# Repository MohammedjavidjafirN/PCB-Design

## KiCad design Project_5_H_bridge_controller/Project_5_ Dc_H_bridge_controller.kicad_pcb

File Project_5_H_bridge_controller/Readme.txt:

This project implements a 12V DC motor driver using an H-Bridge topology, designed to provide bidirectional control and speed regulation of a DC motor. The circuit integrates power electronics and embedded control, using an ESP32 microcontroller to generate PWM control signals and a TC4427A gate driver IC to efficiently drive the MOSFETs.
The H-Bridge is constructed using four N-channel MOSFETs (IRLZ24NPBF) arranged in a full-bridge configuration. This arrangement allows the polarity of the voltage across the motor to be reversed, enabling both forward and reverse rotation. The motor is powered using an external 12V supply, while the switching behavior is controlled through PWM signals from the ESP32.
The PWM signals are fed into the TC4427A dual MOSFET gate driver, which amplifies the control signals and provides sufficient current to rapidly charge and discharge the MOSFET gates. This ensures fast switching, reduced switching losses, and improved efficiency compared to directly driving MOSFETs from the microcontroller.

By controlling the switching sequence of the MOSFETs:

1.One diagonal pair of MOSFETs turns ON → motor rotates in one direction
2.The opposite diagonal pair turns ON → motor reverses direction
3.PWM applied to the enable path → controls motor speed

The design demonstrates a complete motor control system, combining high-current switching, logic-level control, and efficient gate driving

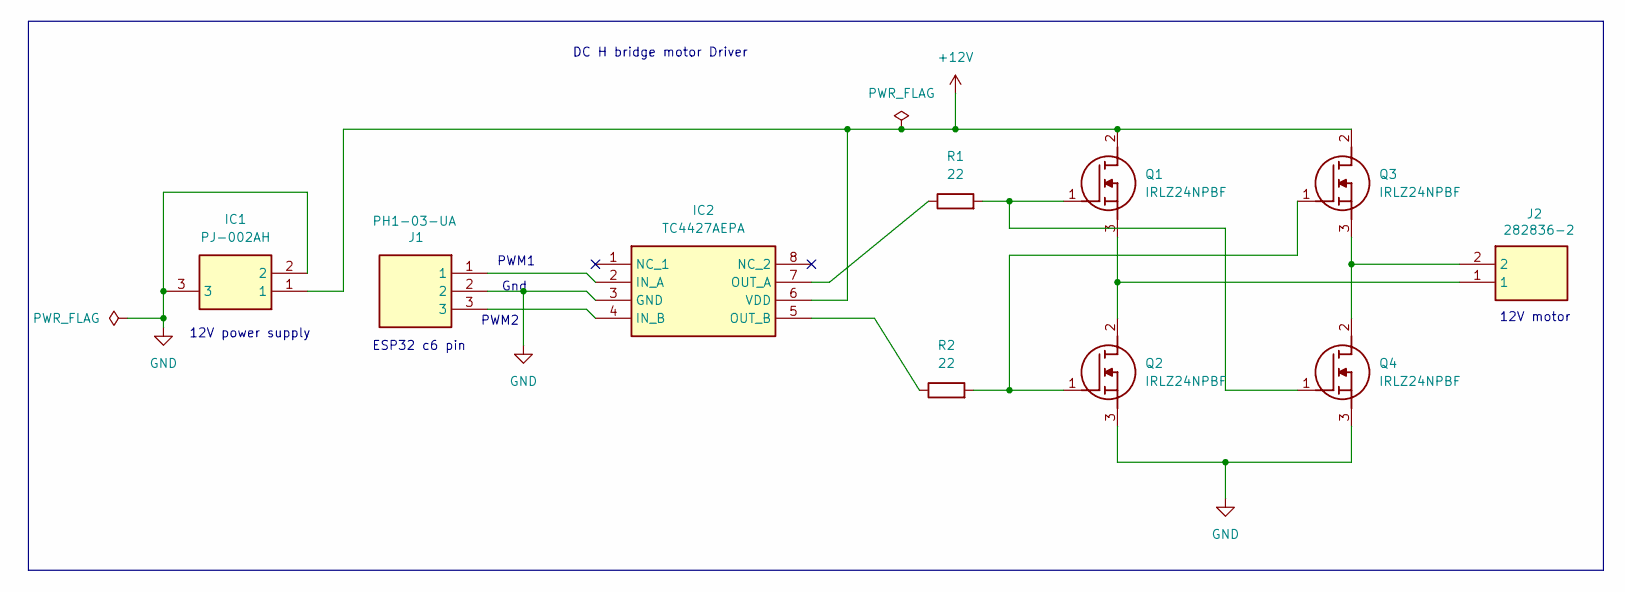
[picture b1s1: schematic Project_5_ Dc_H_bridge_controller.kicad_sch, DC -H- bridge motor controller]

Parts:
IC1: PJ-002AH; PJ002AH; Manufacturer_Part_Number PJ-002AH; Mouser Part Number 490-PJ-002AH
IC2: TC4427AEPA; Manufacturer_Part_Number TC4427AEPA; Mouser Part Number 579-TC4427AEPA
J1: PH1-03-UA; Manufacturer_Part_Number PH1-03-UA; Mouser Part Number 737-PH1-03-UA
J2: 282836-2; 2828362 V2; Manufacturer_Part_Number 282836-2; Mouser Part Number 571-2828362
Q1, Q2, Q3, Q4: IRLZ24NPBF; IRLZ24NBF; Manufacturer_Part_Number IRLZ24NPBF; Mouser Part Number 942-IRLZ24NPBF
R1, R2: 22; R_Axial_DIN0204_L3.6mm_D1.6mm_P5.08mm_Horizontal

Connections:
+12V: IC1.1, IC2.6 (VDD), Q1.2 (D), Q3.2 (D)
GND: IC1.2, IC1.3, IC2.3 (GND), J1.2, Q2.3 (S), Q4.3 (S)
unnamed: IC2.2 (IN_A), J1.1
unnamed: IC2.4 (IN_B), J1.3
unnamed: IC2.7 (OUT_A), R1.1
unnamed: IC2.5 (OUT_B), R2.1
unnamed: Q1.1 (G), Q4.1 (G), R1.2
unnamed: J2.1, Q1.3 (S), Q2.2 (D)
unnamed: Q2.1 (G), Q3.1 (G), R2.2
unnamed: J2.2, Q3.3 (S), Q4.2 (D)

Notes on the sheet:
PWM1
12V power supply
12V motor
PWM2
Gnd
DC H bridge motor Driver
ESP32 c6 pin

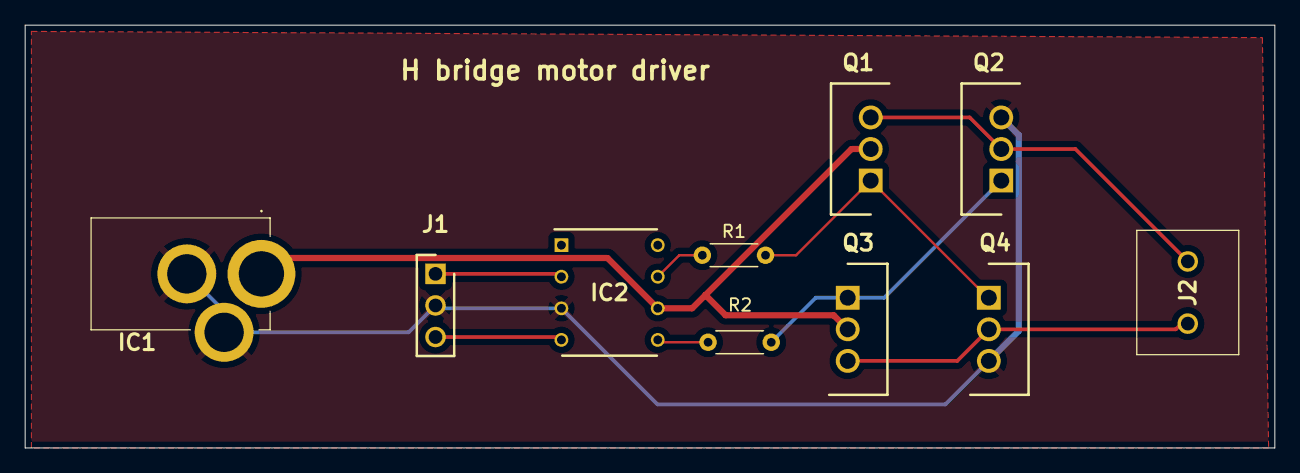
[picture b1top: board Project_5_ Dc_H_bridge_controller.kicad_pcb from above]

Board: 2 copper layers, 100.5 x 34.0 mm, 10 parts (0 on the bottom side), 10 nets.

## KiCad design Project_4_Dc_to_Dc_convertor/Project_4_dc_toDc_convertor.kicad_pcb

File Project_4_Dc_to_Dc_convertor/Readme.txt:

Project description:
This project implements a DC-DC Boost Converter designed to step up a 5V input supply to a regulated 12V output, primarily intended to drive loads such as a DC fan. The design integrates power electronics and embedded control, where the switching operation is driven by PWM signals from an ESP32 microcontroller.
The core of the circuit is based on a boost converter topology, consisting of an inductor, switching MOSFET, diode, and output capacitor. A gate driver IC (TC4427A) is used to efficiently drive the MOSFET, ensuring fast switching and reducing transition losses. The PWM signal from the ESP32 is fed into the gate driver, which amplifies the signal to provide sufficient current for driving the MOSFET gate.
During operation, when the MOSFET is switched ON, energy is stored in the inductor. When the MOSFET is switched OFF, the stored energy is released through the diode to the output capacitor, resulting in a boosted output voltage higher than the input. The output capacitor smooths the voltage, providing a stable DC output suitable for powering a 12V fan.
The switching frequency and duty cycle of the PWM signal control the output voltage, allowing dynamic adjustment of the boost level. This makes the system flexible for different load conditions and demonstrates real-time control of power conversion using a microcontroller.

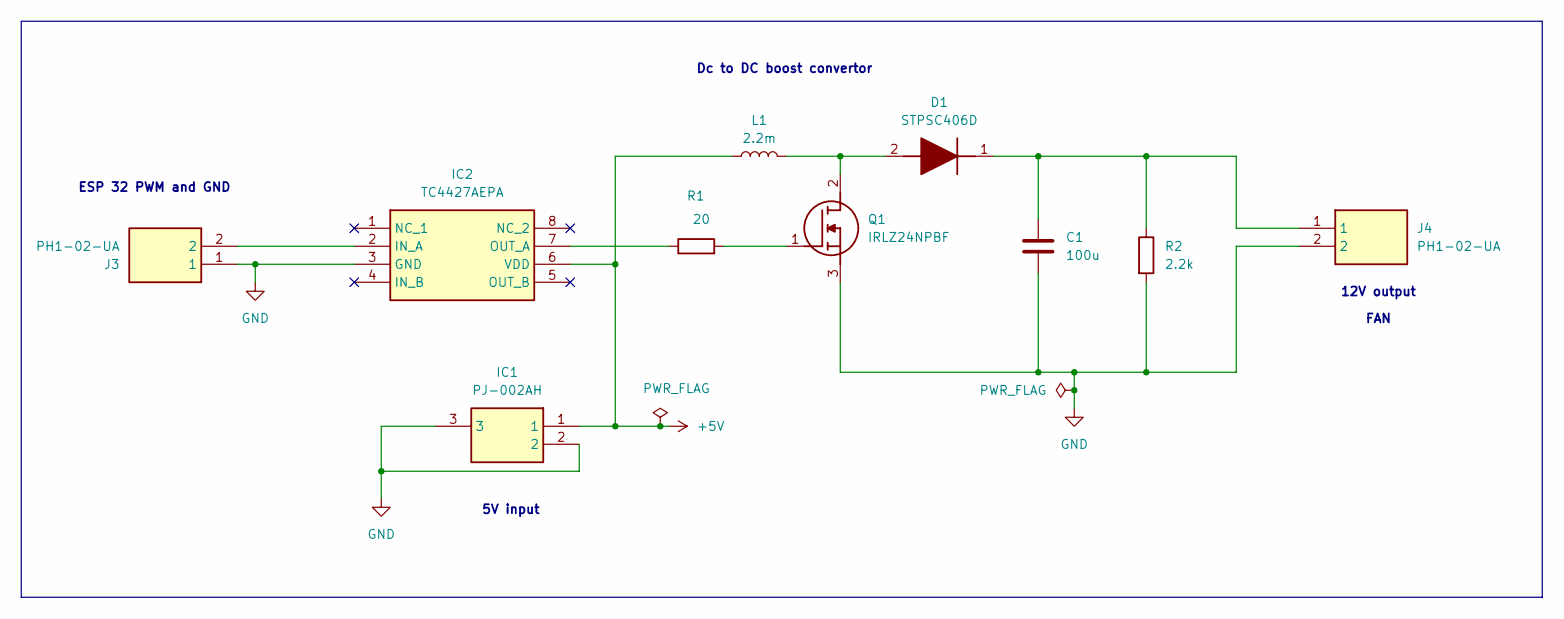
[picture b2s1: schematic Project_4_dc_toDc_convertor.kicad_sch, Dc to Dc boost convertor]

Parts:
C1: 100u; C_Radial_D5.0mm_H11.0mm_P2.00mm
D1: STPSC406D; STPSC4063; Manufacturer_Part_Number STPSC406D; Mouser Part Number 511-STPSC406D
IC1: PJ-002AH; PJ002AH.kicad_mod_v2; Manufacturer_Part_Number PJ-002AH; Mouser Part Number 490-PJ-002AH
IC2: TC4427AEPA; DIP775W51P254L978H508Q8N; Manufacturer_Part_Number TC4427AEPA; Mouser Part Number 579-TC4427AEPA
J3, J4: PH1-02-UA; PH1-02-UA-j3; Manufacturer_Part_Number PH1-02-UA; Mouser Part Number 737-PH1-02-UA
L1: 2.2m; L_Radial_D10.0mm_P5.00mm_Fastron_07M
Q1: IRLZ24NPBF; Manufacturer_Part_Number IRLZ24NPBF; Mouser Part Number 942-IRLZ24NPBF
R1: 20; R_Axial_DIN0204_L3.6mm_D1.6mm_P7.62mm_Horizontal
R2: 2.2k; R_Axial_DIN0204_L3.6mm_D1.6mm_P7.62mm_Horizontal

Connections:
+5V: IC1.1, IC2.6 (VDD), L1.1
GND: C1.2, IC1.2, IC1.3, IC2.3 (GND), J3.1, J4.2, Q1.3 (S), R2.2
unnamed: D1.2 (A), L1.2, Q1.2 (D)
unnamed: C1.1, D1.1 (K), J4.1, R2.1
unnamed: IC2.2 (IN_A), J3.2
unnamed: IC2.7 (OUT_A), R1.1
unnamed: Q1.1 (G), R1.2

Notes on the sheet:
FAN
Dc to DC boost convertor
5V input
12V output
ESP 32 PWM and GND

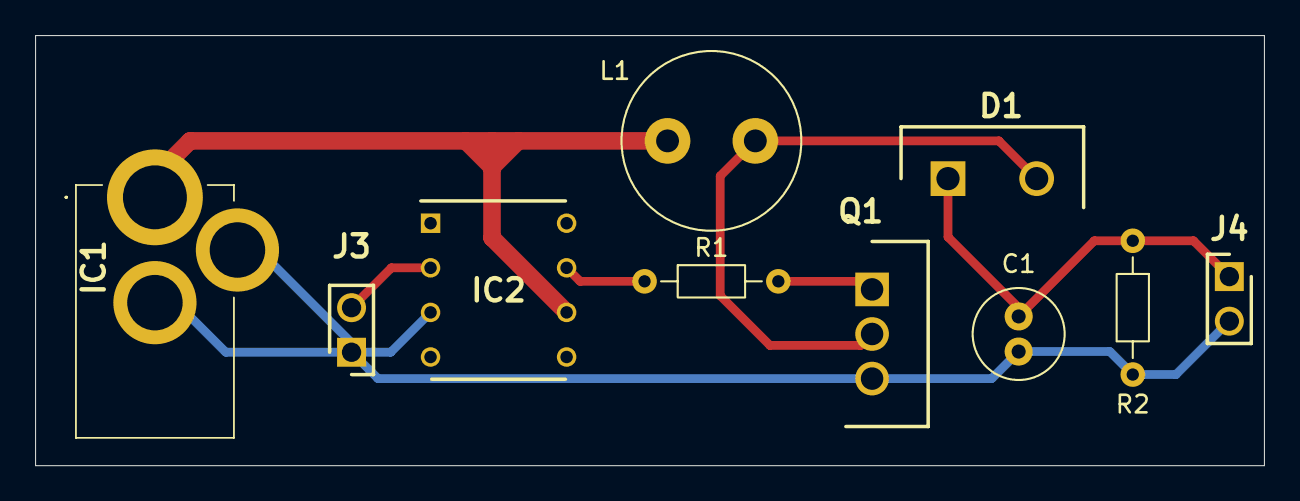
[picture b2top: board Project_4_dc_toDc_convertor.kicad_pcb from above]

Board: 2 copper layers, 70.0 x 24.5 mm, 10 parts (0 on the bottom side), 7 nets.

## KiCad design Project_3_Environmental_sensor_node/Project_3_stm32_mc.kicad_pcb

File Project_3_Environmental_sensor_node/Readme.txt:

Project description:
This project is a custom STM32-based microcontroller development board designed around the STM32F401RE MCU, intended to function as a compact environmental sensor node. The board integrates multiple communication interfaces, stable power regulation, and analog signal conditioning to support real-world embedded applications.The system is powered through a USB OTG interface, which provides the primary input supply (VBUS). This voltage is regulated down to 3.3V using the AMS1117 linear regulator, ensuring a stable operating voltage for the microcontroller and associated peripherals. To further enhance analog performance, a dedicated VDDA filtering network (ferrite bead and decoupling capacitors) is implemented to isolate noise from the digital supply, improving the accuracy of ADC-based sensor readings.

At the core of the design, the STM32F401RE microcontroller manages data acquisition, processing, and communication. The board exposes multiple communication protocols, including:
UART for serial communication and debugging
I2C for interfacing with environmental sensors (e.g., temperature, humidity, pressure)
SPI for high-speed peripheral communication
SWD (Serial Wire Debug) for programming and debugging

An external crystal oscillator is used to provide a stable clock source, ensuring reliable timing for communication protocols and internal operations. Proper decoupling capacitors are placed near the power pins of the MCU to minimize voltage fluctuations and ensure stable performance.The design also includes dedicated header pins for GPIO expansion, enabling easy integration with external modules and sensors. The USB interface supports both power delivery and potential data communication, making the board versatile for embedded system development.

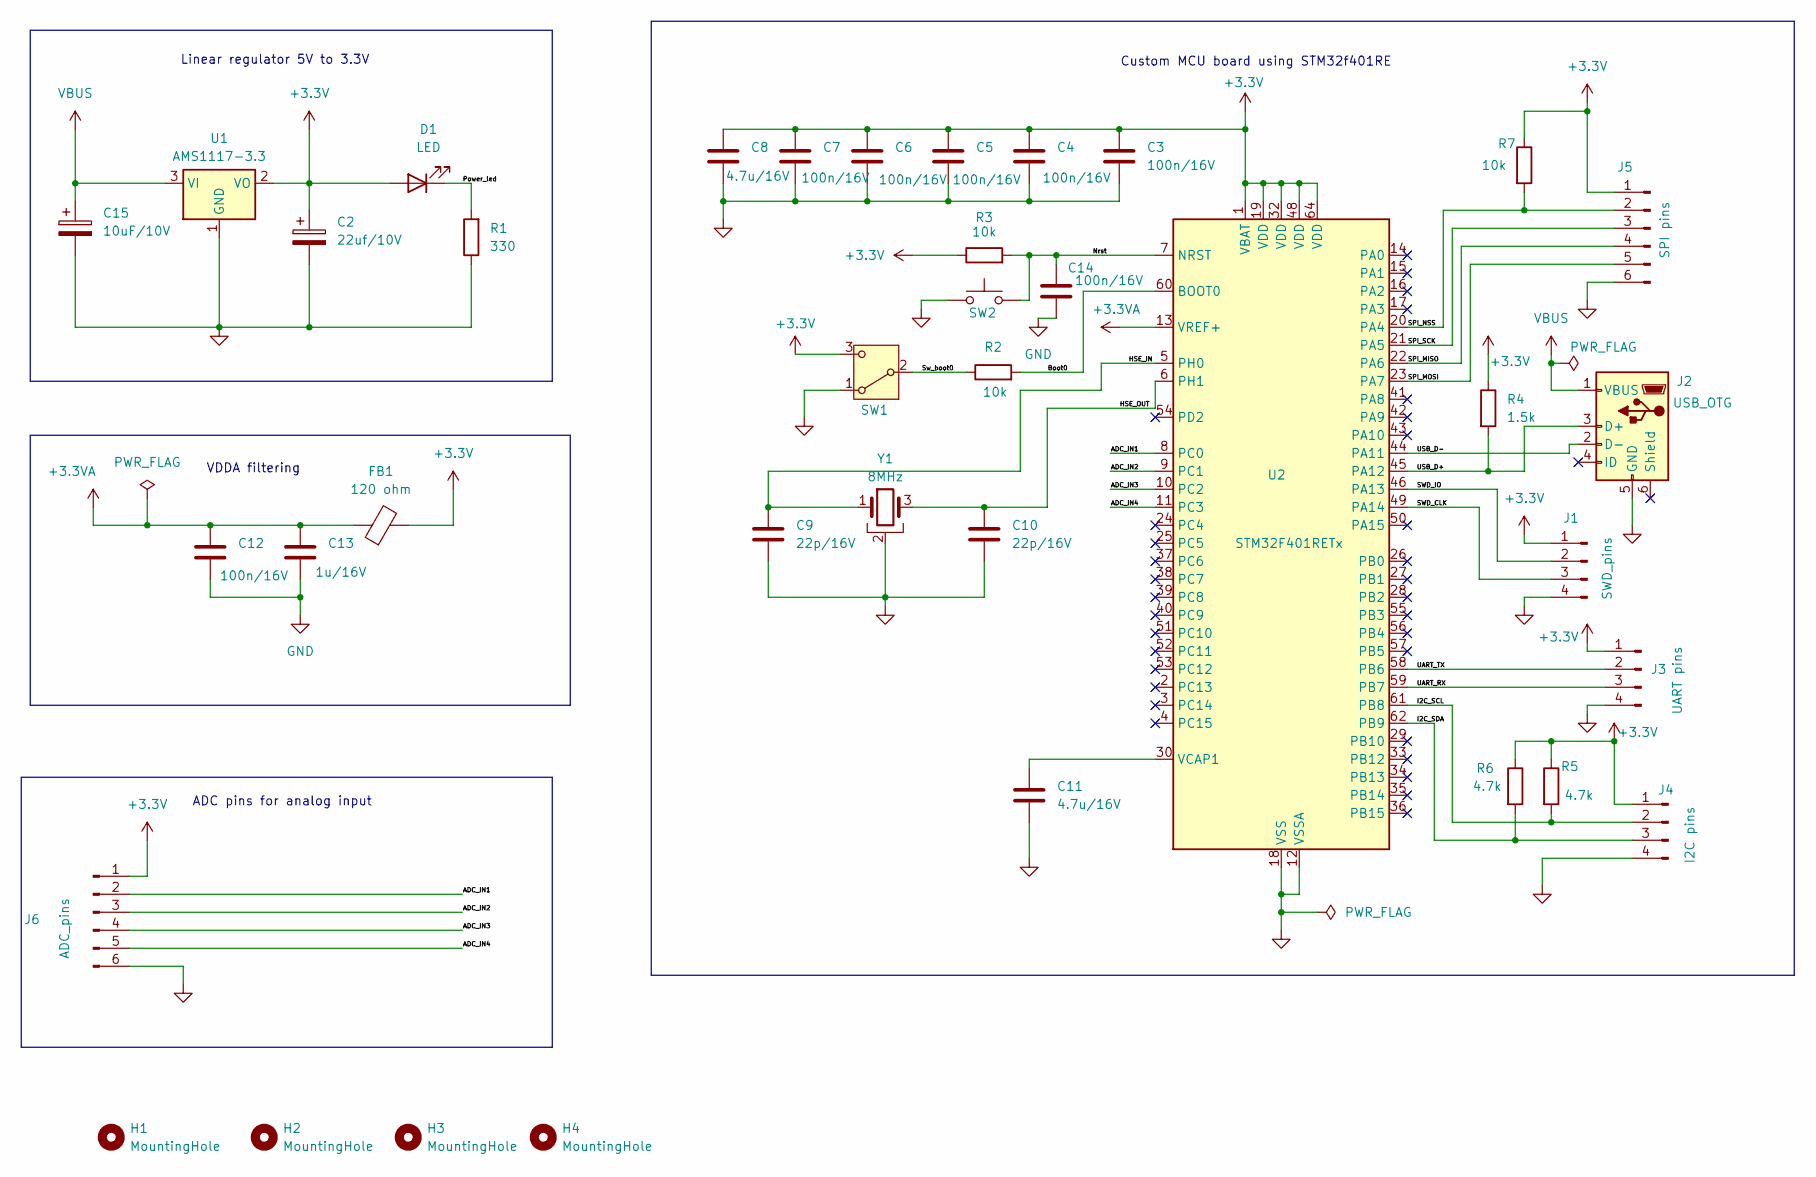
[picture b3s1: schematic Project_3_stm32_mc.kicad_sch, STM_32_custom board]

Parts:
C2: 22uf/10V; CP_EIA-1608-08_AVX-J
C3, C4, C5, C6, C7, C14: 100n/16V; C_0603_1608Metric
C8, C11: 4.7u/16V; C_0805_2012Metric
C9, C10: 22p/16V; C_0805_2012Metric
C12: 100n/16V; C_0402_1005Metric
C13: 1u/16V; C_0402_1005Metric
C15: 10uF/10V; CP_EIA-1608-08_AVX-J
D1: LED; LED_0603_1608Metric
FB1: 120 ohm; L_0603_1608Metric
H1, H2, H3, H4: MountingHole; MountingHole_2.5mm_Pad
J1: SWD_pins; PinHeader_1x04_P2.00mm_Vertical
J2: USB_OTG; USB_Mini-B_Lumberg_2486_01_Horizontal
J3: UART pins; PinHeader_1x04_P2.00mm_Vertical
J4: I2C pins; PinHeader_1x04_P2.00mm_Vertical
J5: SPI pins; PinHeader_1x06_P2.54mm_Vertical
J6: ADC_pins; JST_PH_B6B-PH-K_1x06_P2.00mm_Vertical
R1: 330; R_0603_1608Metric
R2, R3, R7: 10k; R_0603_1608Metric
R4: 1.5k; R_0603_1608Metric
R5, R6: 4.7k; R_0603_1608Metric
SW1: SW_SPDT; SW_SPDT_PCM12
SW2: SW_Push; SW_Push_1P1T_NO_CK_KMR2
U1: AMS1117-3.3; SOT-223-3_TabPin2
U2: STM32F401RETx; LQFP-64_10x10mm_P0.5mm
Y1: 8MHz; Crystal_SMD_MicroCrystal_MS1V-T1K

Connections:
+3.3VA: C12.1, C13.1, FB1.1, U2.13 (VREF+)
/ADC_IN1: J6.2, U2.8 (PC0)
/ADC_IN2: J6.3, U2.9 (PC1)
/ADC_IN3: J6.4, U2.10 (PC2)
/ADC_IN4: J6.5, U2.11 (PC3)
/Boot0: R2.2, U2.60 (BOOT0)
/HSE_IN: C9.1, U2.5 (PH0), Y1.1
/HSE_OUT: C10.1, U2.6 (PH1), Y1.3
/I2C_SCL: J4.2, R5.2, U2.61 (PB8)
/I2C_SDA: J4.3, R6.2, U2.62 (PB9)
/Power_led: D1.1 (K), R1.2
/SPI_MISO: J5.4, U2.22 (PA6)
/SPI_MOSI: J5.5, U2.23 (PA7)
/SPI_NSS: J5.2, R7.2, U2.20 (PA4)
/SPI_SCK: J5.3, U2.21 (PA5)
/SWD_CLK: J1.3, U2.49 (PA14)
/SWD_IO: J1.2, U2.46 (PA13)
/Sw_boot0: R2.1, SW1.2 (B)
/UART_RX: J3.3, U2.59 (PB7)
/UART_TX: J3.2, U2.58 (PB6)
/USB_D+: J2.3 (D+), R4.2, U2.45 (PA12)
/USB_D-: J2.2 (D-), U2.44 (PA11)
GND: C2.2, C3.2, C4.2, C5.2, C6.2, C7.2, C8.2, C9.2, C10.2, C11.2, C12.2, C13.2, C14.2, C15.2, J1.4, J2.5 (GND), J3.4, J4.4, J5.6, J6.6, R1.1, SW1.1 (A), SW2.1, U1.1 (GND), U2.12 (VSSA), U2.18 (VSS), U2.31 (VSS), U2.47 (VSS), U2.63 (VSS), Y1.2; also elsewhere on the board
unnamed: C11.1, U2.30 (VCAP1)
VBUS: C15.1, J2.1 (VBUS), U1.3 (VI); also elsewhere on the board

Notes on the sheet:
Custom MCU board using STM32f401RE
ADC pins for analog input
Linear regulator 5V to 3.3V
VDDA filtering

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
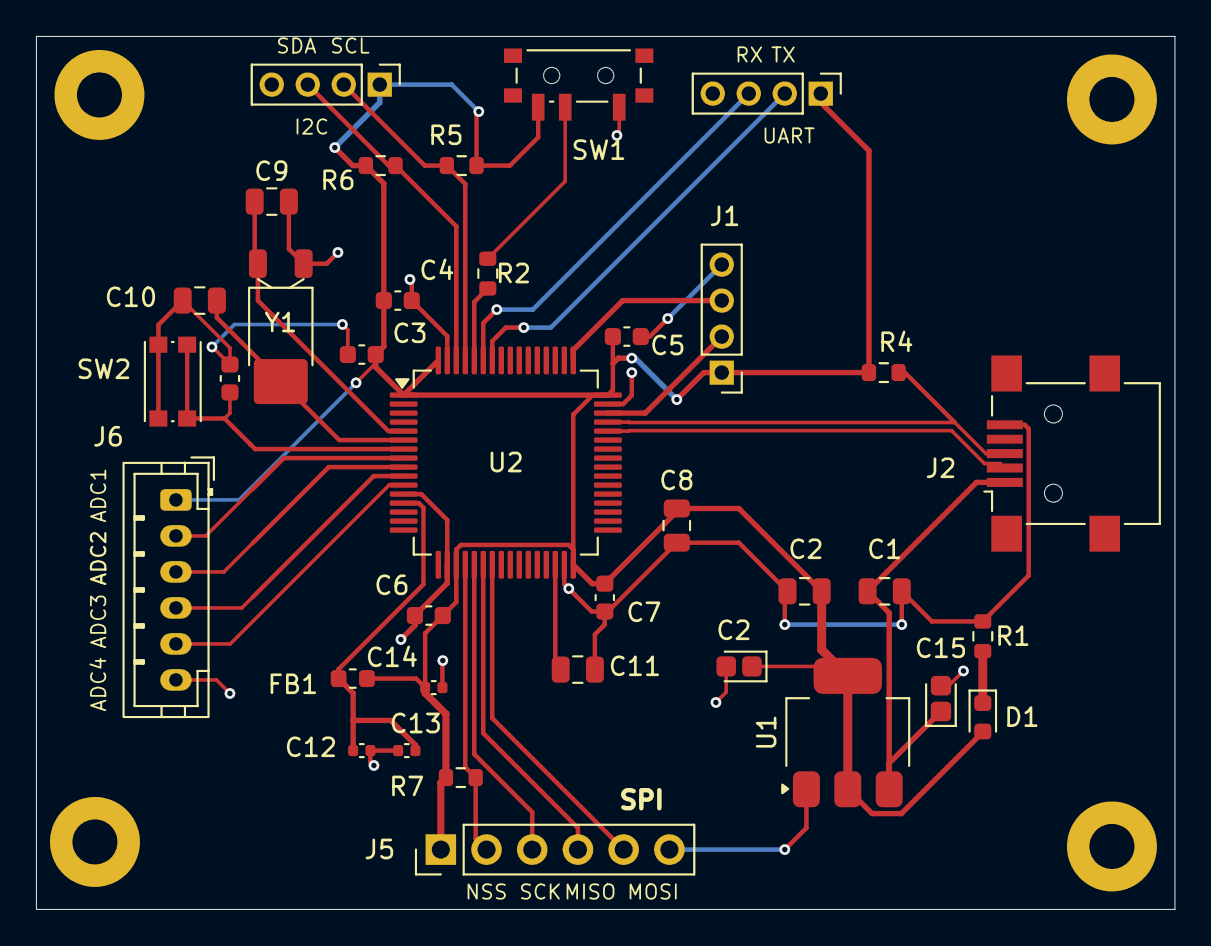
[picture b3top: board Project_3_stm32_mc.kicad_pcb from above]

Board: 2 copper layers, 63.2 x 48.5 mm, 40 parts (0 on the bottom side), 27 nets.

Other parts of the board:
C1: 10u / 16V; C_0805_2012Metric
C2#2: 22uf/10V; CP_EIA-1608-08_AVX-J
C14#2: 100n/16V; C_0603_1608Metric

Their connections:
GND: C1.2, C2#2.2, C14#2.2; also elsewhere on the board
VBUS: C1.1; also elsewhere on the board

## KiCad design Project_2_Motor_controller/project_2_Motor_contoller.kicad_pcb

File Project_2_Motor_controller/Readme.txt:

Project description:
This project is a dual DC motor controller PCB designed using the L298N motor driver IC, integrated with a linear voltage regulator to provide a stable power supply for control logic. The board is capable of controlling two DC motors independently, making it suitable for basic robotics and embedded control applications
The L298N is a dual H-bridge motor driver, which allows bidirectional control of motors by switching the polarity of the voltage applied to each motor. Control signals are provided through input pins (IN1, IN2, IN3, IN4), enabling forward, reverse, and stop operations for each motor. Additionally, enable pins (ENA, ENB) can be used for speed control via PWM signals
The circuit accepts an external power input (e.g., 12V), which is used to drive the motors. A linear voltage regulator is incorporated to step down and regulate this input voltage to a stable 5V supply, ensuring reliable operation of logic components and external control interfaces such as microcontrollers.
Flyback diodes are included in the design to protect the circuit from back EMF generated by the motors, improving the overall reliability and durability of the system. Capacitors are used for filtering and stabilizing the power supply, reducing noise and voltage fluctuations during motor operation.

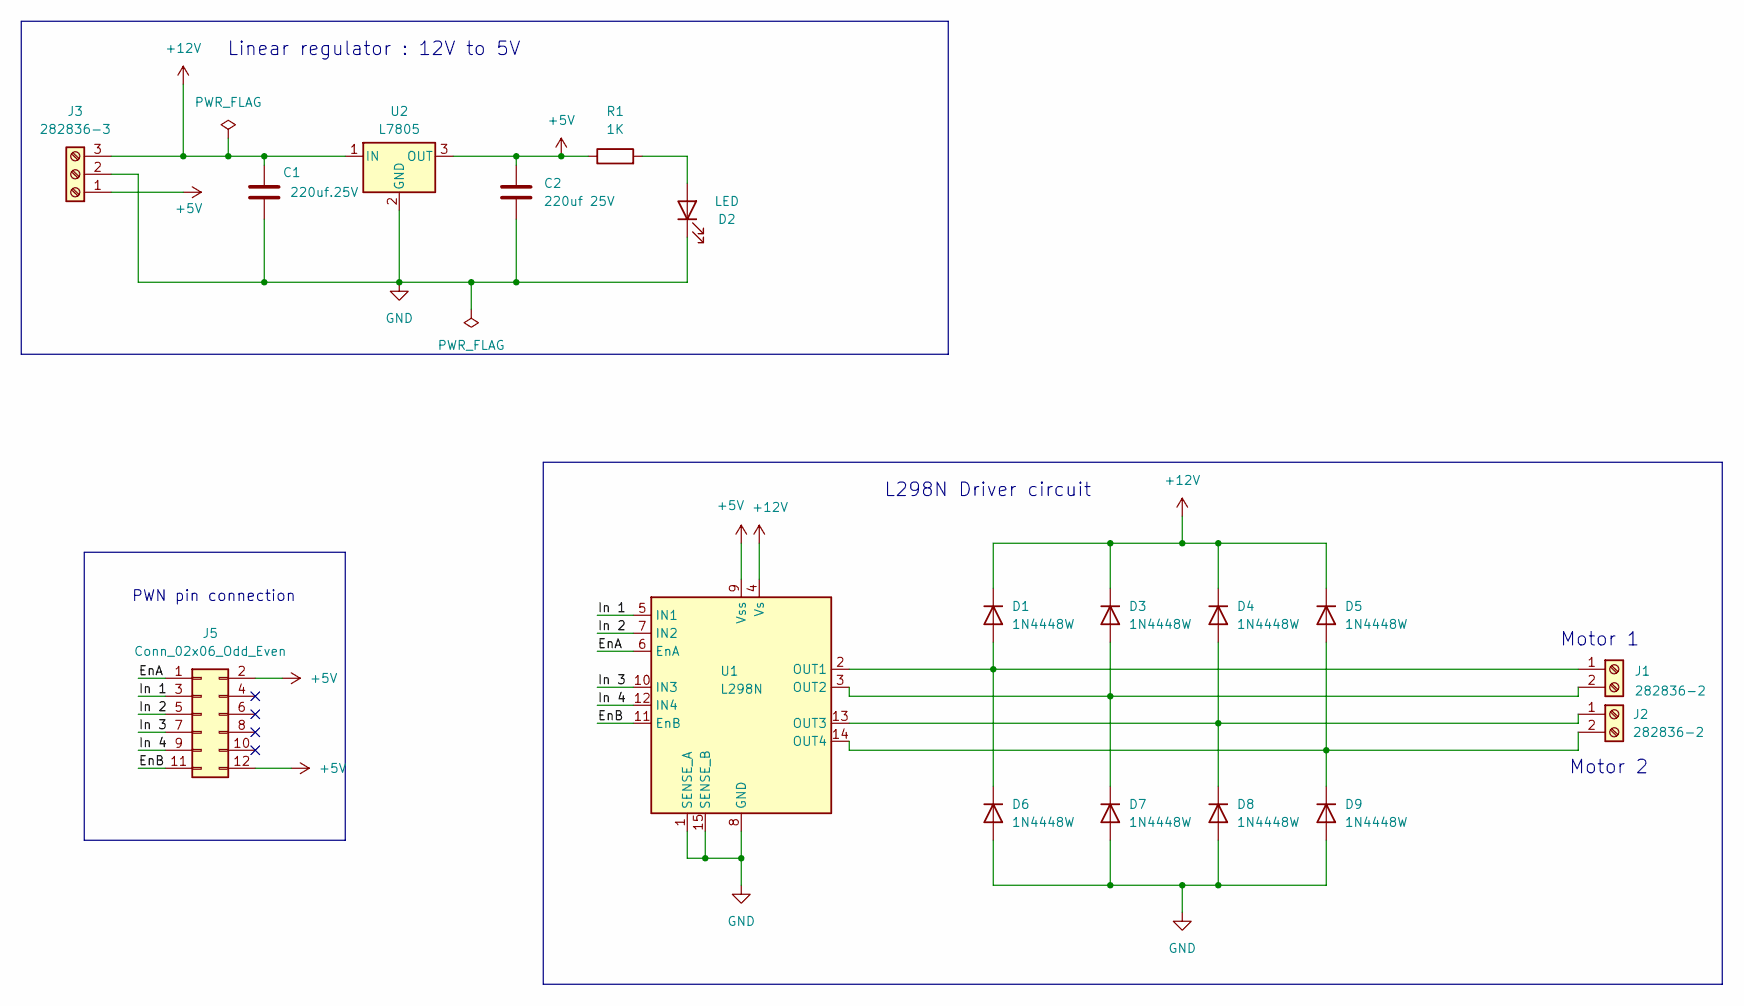
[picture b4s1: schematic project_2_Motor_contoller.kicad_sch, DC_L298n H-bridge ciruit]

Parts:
C1: 220uf.25V; C_Radial_D8.0mm_H7.0mm_P3.50mm
C2: 220uf 25V; C_Radial_D8.0mm_H7.0mm_P3.50mm
D1, D3, D4, D5, D6, D7, D8, D9: 1N4448W; D_SOD-123
D2: LED; LED_0603_1608Metric
J1, J2: 282836-2; TerminalBlock_Phoenix_MKDS-1,5-2-5.08_1x02_P5.08mm_Horizont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
J3: 282836-3; TerminalBlock_Phoenix_MKDS-1,5-3-5.08_1x03_P5.08mm_Horizont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
J5: Conn_02x06_Odd_Even; PinHeader_2x06_P2.54mm_Vertical
R1: 1K; R_0603_1608Metric
U1: L298N; TO-220-15_P2.54x5.08mm_StaggerOdd_Lead4.58mm_Vertical
U2: L7805; TO-263-2

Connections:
+5V: C2.1, J3.1, J5.2, J5.12, R1.1, U1.9 (Vss), U2.3 (OUT)
+12V: C1.1, D1.1 (K), D3.1 (K), D4.1 (K), D5.1 (K), J3.3, U1.4 (Vs), U2.1 (IN)
/EnA: J5.1, U1.6 (EnA)
/EnB: J5.11, U1.11 (EnB)
/In 1: J5.3, U1.5 (IN1)
/In 2: J5.5, U1.7 (IN2)
/In 3: J5.7, U1.10 (IN3)
/In 4: J5.9, U1.12 (IN4)
GND: C1.2, C2.2, D2.1 (K), D6.2 (A), D7.2 (A), D8.2 (A), D9.2 (A), J3.2, U1.1 (SENSE_A), U1.8 (GND), U1.15 (SENSE_B), U2.2 (GND)
unnamed: D1.2 (A), D6.1 (K), J1.1, U1.2 (OUT1)
unnamed: D2.2 (A), R1.2
unnamed: D3.2 (A), D7.1 (K), J1.2, U1.3 (OUT2)
unnamed: D4.2 (A), D8.1 (K), J2.1, U1.13 (OUT3)
unnamed: D5.2 (A), D9.1 (K), J2.2, U1.14 (OUT4)

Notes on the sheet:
Motor 1
Motor 2
L298N Driver circuit
PWN pin connection
Linear regulator : 12V to 5V

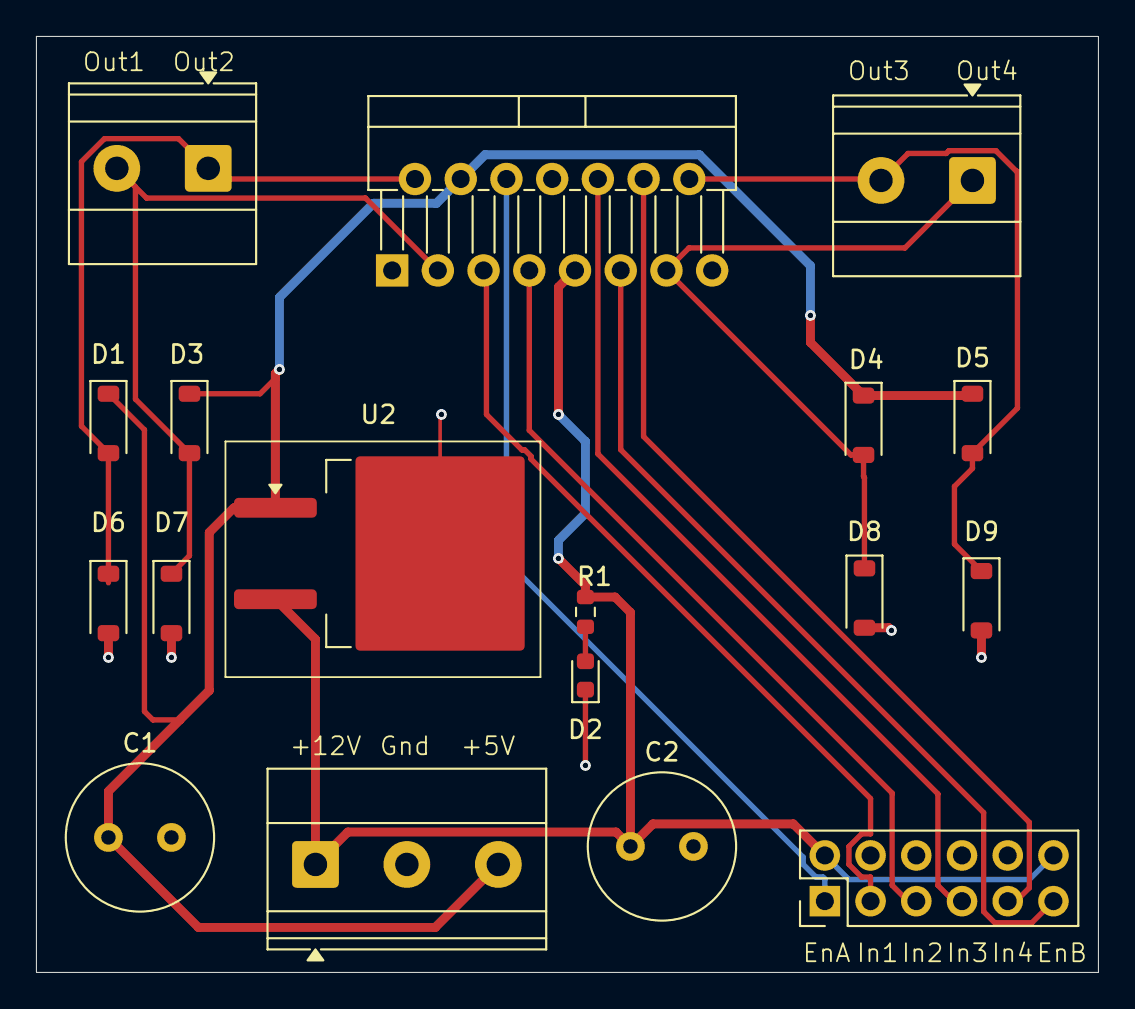
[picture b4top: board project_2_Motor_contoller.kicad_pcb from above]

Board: 2 copper layers, 59.0 x 52.0 mm, 18 parts (0 on the bottom side), 14 nets.

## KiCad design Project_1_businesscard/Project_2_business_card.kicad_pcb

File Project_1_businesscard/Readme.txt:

Project description:
This project is a 555 timer-based LED blinker circuit implemented on a compact PCB designed in the form of a business card. The circuit operates using a timer IC configured in astable mode, where it continuously generates a square wave signal without requiring any external trigger.
When powered by the onboard coin cell battery, the timer IC alternates between charging and discharging cycles through a resistor-capacitor (RC) network. This periodic charging and discharging action produces a continuous oscillating output at the timer’s output pin. As a result, the connected LED turns ON and OFF repeatedly, creating a visible blinking effect. The blinking rate is determined by the values of the resistor and capacitor used in the timing circuit. A slide switch is incorporated to control the power supply, allowing the user to turn the circuit ON or OFF as needed.

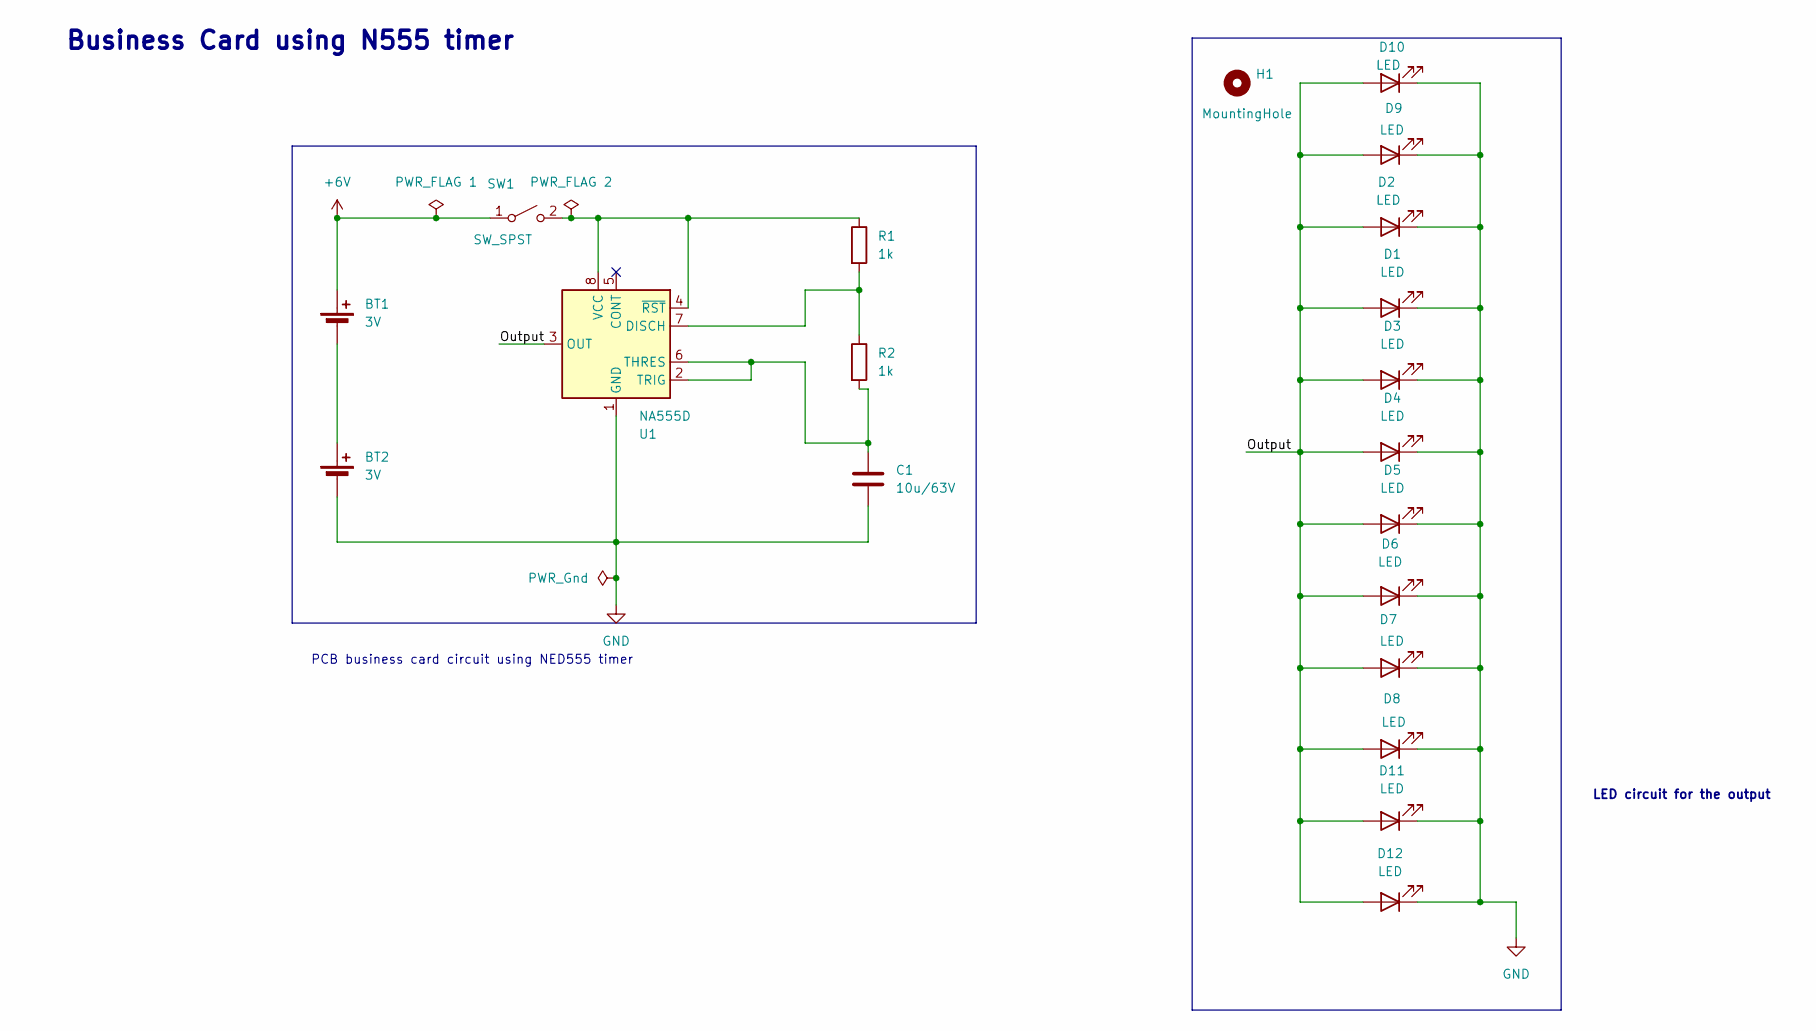
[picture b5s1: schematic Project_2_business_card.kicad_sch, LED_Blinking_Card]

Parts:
BT1, BT2: 3V; BatteryHolder_Keystone_3034_1x20mm
C1: 10u/63V; C_Radial_D4.0mm_H7.0mm_P1.50mm
D1, D2, D3, D4, D5, D6, D7, D8, D9, D10, D11, D12: LED; LED_0805_2012Metric
H1: MountingHole; MountingHole_2.1mm
R1, R2: 1k; R_0603_1608Metric
SW1: SW_SPST; SW_DIP_SPSTx01_Slide_9.78x4.72mm_W8.61mm_P2.54mm
U1: NA555D; SOIC-8_3.9x4.9mm_P1.27mm

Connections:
+6V: BT1.1 (+), SW1.1 (A)
/Output: D1.2 (A), D2.2 (A), D3.2 (A), D4.2 (A), D5.2 (A), D6.2 (A), D7.2 (A), D8.2 (A), D9.2 (A), D10.2 (A), D11.2 (A), D12.2 (A), U1.3 (OUT)
GND: BT2.2 (-), C1.2, D1.1 (K), D2.1 (K), D3.1 (K), D4.1 (K), D5.1 (K), D6.1 (K), D7.1 (K), D8.1 (K), D9.1 (K), D10.1 (K), D11.1 (K), D12.1 (K), U1.1 (GND)
unnamed: BT1.2 (-), BT2.1 (+)
unnamed: R1.1, SW1.2 (B), U1.4 (~RST), U1.8 (VCC)
unnamed: R1.2, R2.1, U1.7 (DISCH)
unnamed: C1.1, R2.2, U1.2 (TRIG), U1.6 (THRES)

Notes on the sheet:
Business Card using N555 timer
PCB business card circuit using NED555 timer
LED circuit for the output

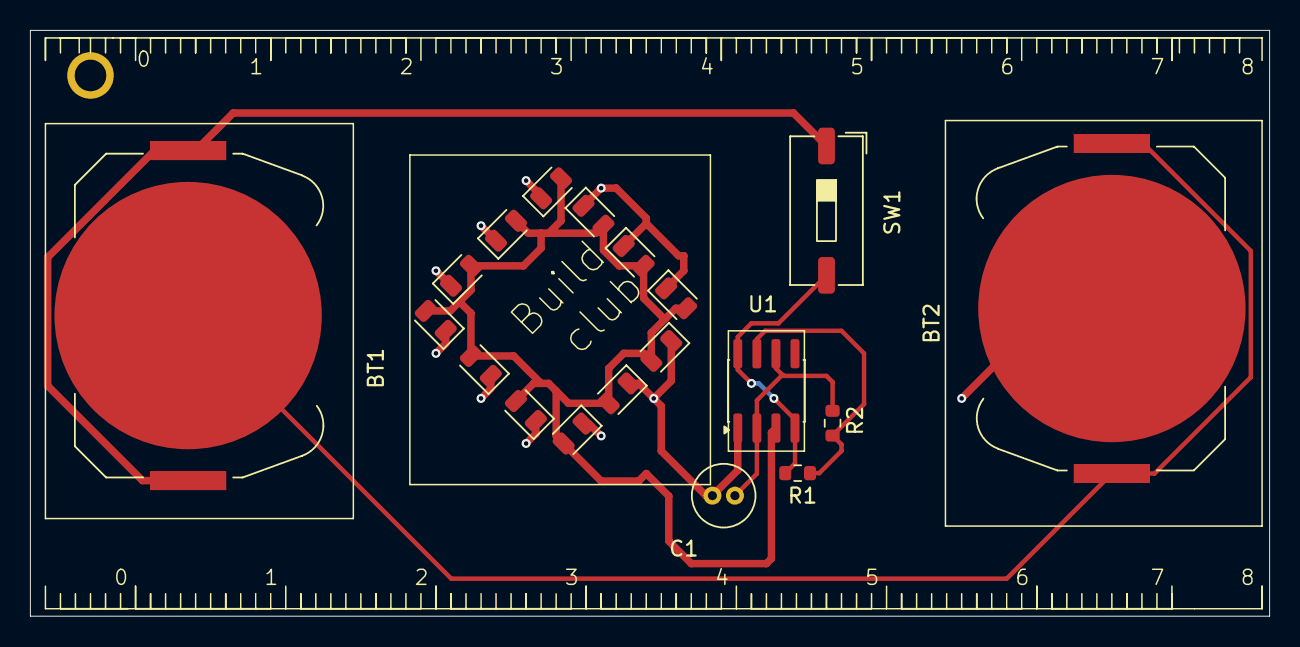
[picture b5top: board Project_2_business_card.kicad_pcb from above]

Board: 2 copper layers, 82.5 x 39.0 mm, 20 parts (0 on the bottom side), 7 nets.

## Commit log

2026-03-20 Create Description
